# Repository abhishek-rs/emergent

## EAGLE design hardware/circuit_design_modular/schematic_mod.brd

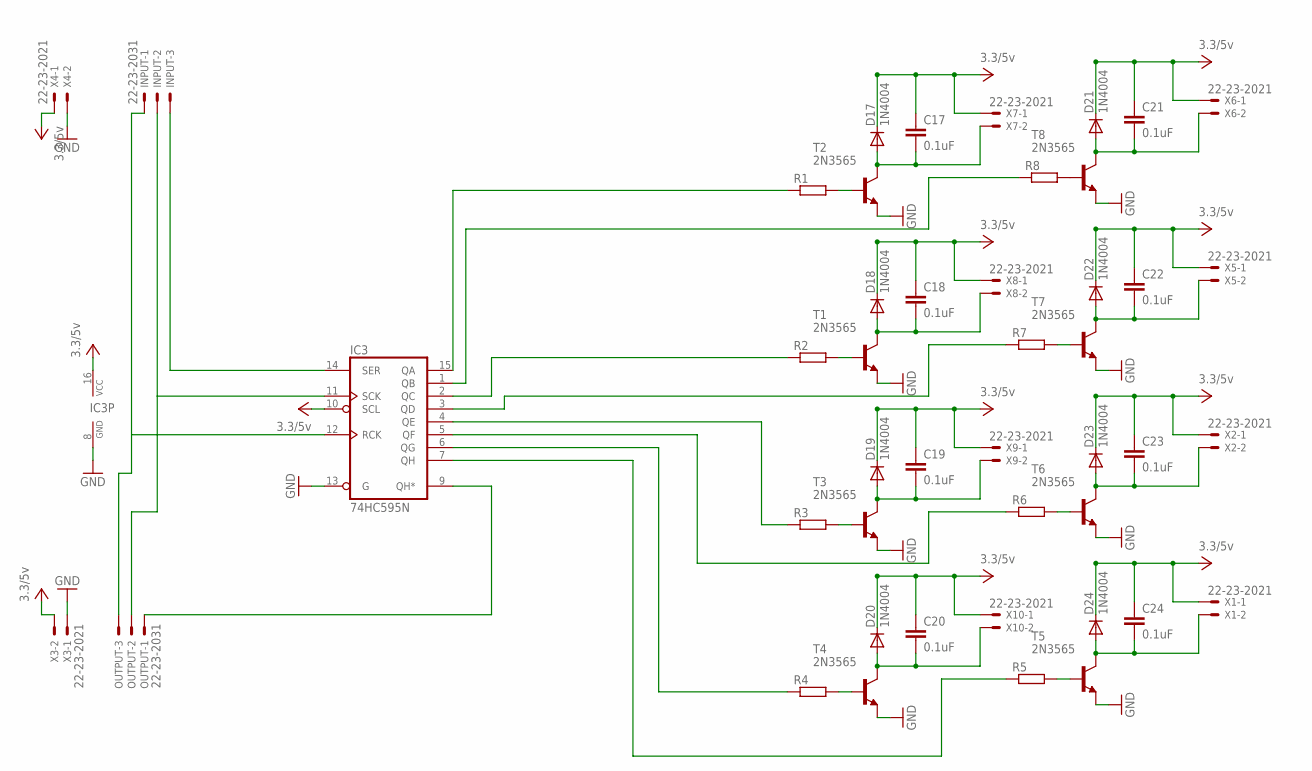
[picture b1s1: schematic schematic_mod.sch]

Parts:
C17, C18, C19, C20, C21, C22, C23, C24: 0.1uF; C025-024X044
D17, D18, D19, D20, D21, D22, D23, D24: 1N4004; DO41-10
IC3: 74HC595N; DIL16
INPUT: 22-23-2031
OUTPUT: 22-23-2031
R1, R2, R3, R4, R5, R6, R7, R8: R-EU_0207/7; 0207/7
T1, T2, T3, T4, T5, T6, T7, T8: 2N3565; TO92
X1, X2, X3, X4, X5, X6, X7, X8, X9, X10: 22-23-2021

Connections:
GND: IC3.8 (GND), IC3.13 (G), T1.3 (E), T2.3 (E), T3.3 (E), T4.3 (E), T5.3 (E), T6.3 (E), T7.3 (E), T8.3 (E), X3.1, X4.2
unnamed: R8.2, T8.2 (B)
unnamed: C17.2, D17.A, T2.1 (C), X7.2
unnamed: R1.2, T2.2 (B)
unnamed: C18.2, D18.A, T1.1 (C), X8.2
unnamed: R2.2, T1.2 (B)
unnamed: C19.2, D19.A, T3.1 (C), X9.2
unnamed: R3.2, T3.2 (B)
unnamed: C20.2, D20.A, T4.1 (C), X10.2
unnamed: R4.2, T4.2 (B)
unnamed: C21.2, D21.A, T8.1 (C), X6.2
unnamed: C22.2, D22.A, T7.1 (C), X5.2
unnamed: R7.2, T7.2 (B)
unnamed: C23.2, D23.A, T6.1 (C), X2.2
unnamed: R6.2, T6.2 (B)
unnamed: C24.2, D24.A, T5.1 (C), X1.2
unnamed: R5.2, T5.2 (B)
unnamed: IC3.15 (QA), R1.1
unnamed: IC3.1 (QB), R8.1
unnamed: IC3.2 (QC), R2.1
unnamed: IC3.3 (QD), R7.1
unnamed: IC3.4 (QE), R3.1
unnamed: IC3.5 (QF), R6.1
unnamed: IC3.6 (QG), R4.1
unnamed: IC3.7 (QH), R5.1
unnamed: IC3.14 (SER), INPUT.3
unnamed: IC3.9 (QH*), OUTPUT.1
unnamed: IC3.11 (SCK), INPUT.2, OUTPUT.2
unnamed: IC3.12 (RCK), INPUT.1, OUTPUT.3
VCC: C17.1, C18.1, C19.1, C20.1, C21.1, C22.1, C23.1, C24.1, D17.C, D18.C, D19.C, D20.C, D21.C, D22.C, D23.C, D24.C, IC3.10 (SCL), IC3.16 (VCC), X1.1, X2.1, X3.2, X4.1, X5.1, X6.1, X7.1, X8.1, X9.1, X10.1

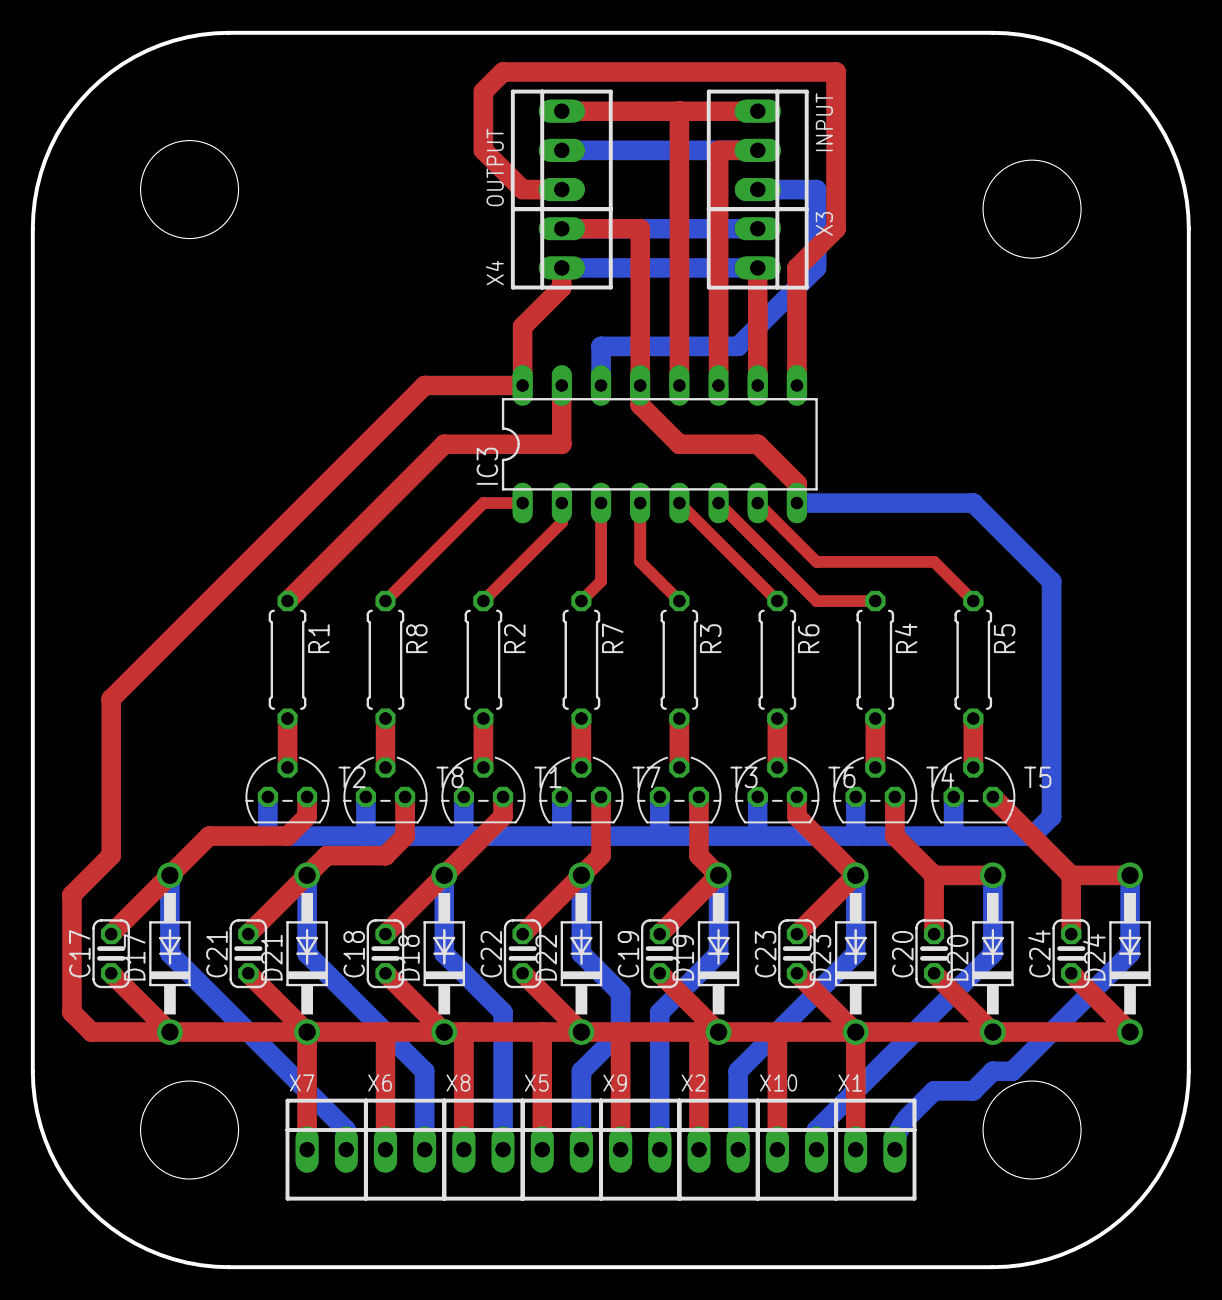
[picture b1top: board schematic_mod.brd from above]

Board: 2 copper layers, 74.9 x 80.0 mm, 45 parts (0 on the bottom side), 30 nets.

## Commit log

2017-03-18 some changes I don't remember
2017-03-18 before pull
2017-04-03 rand
